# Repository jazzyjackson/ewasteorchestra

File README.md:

ewasteorchestra
===============

A group of schematics and code for building instruments out of ewaste

<h3>USB powered Hard Drive Amplifier</h3>

<h3>Harddrive Guitar using Arduino, Firmata, and Pd-Extended</h3>

<p> Works with the latest Firmata as of 4/20/2016 as distributed with Arduino 1.6.8. Sound synthesis by <a href="http://puredata.info/downloads/pd-extended">pd-extended version 0.43.4</a>, which is apparently deprecated but I'll have to catch up another time.</p>
<p> The arduino object (a.k.a. <a href="http://puredata.info/downloads/pduino">pduino</a>) by <a href="http://www.at.or.at/hans/pd/objects.html">Hans-Christoph Steiner</a> is distributed in the same folder as harddrivepackage.pd for out of the box functionality. </p>

<p> The pd sketch takes the analog inputs of the arduino (which should have SimpleAnalogFirmata flashed to memory via the Arduino IDE) and controls the volume of six oscillator objects. The MIDI value of those oscillator objects are triggered by a USB numpad. Being that the output of the DC motors in the harddrives are AC sinewaves, and the Arduino's ADC is only positive voltage at a certain sample rate, the program sums recent samples from each input while also constantly substracting from that sum over time, so the effect is that the faster you spin the hard disk, the faster you reach max volume. As soon as the harddrive stops spinning, the sum is quickly decremented to 0.  This happens in the fade subpatch of the chordfader subpatch. It's quite ugly and I wrote it before I knew about the line~ function so its not perfect. </p>

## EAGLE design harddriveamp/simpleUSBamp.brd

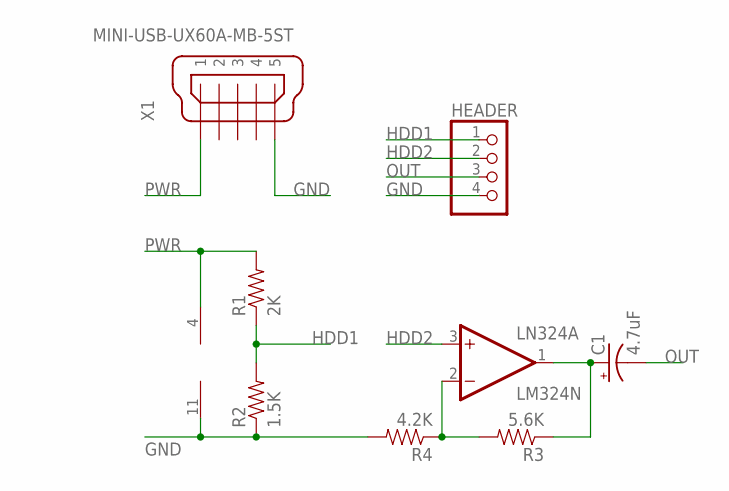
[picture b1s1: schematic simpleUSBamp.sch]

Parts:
C1: 4.7uF; CPOL-RADIAL-100UF-25V
HEADER: PINHD-1X4; 1X04
LN324: LM324N; DIL14
R1: 2K; AXIAL-0.4
R2: 1.5K; AXIAL-0.4
R3: 5.6K; AXIAL-0.4
R4: 4.2K; AXIAL-0.4
X1: MINI-USB-UX60A-MB-5ST; UX60A-MB-5ST

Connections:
GND: HEADER.4, LN324.11 (V-), R2.P$1 (1), R4.P$2 (2), X1.5
HDD1: HEADER.1, R1.P$1 (1), R2.P$2 (2)
HDD2: HEADER.2, LN324.3 (+IN)
unnamed: C1.1 (+), LN324.1 (OUT), R3.P$1 (1)
unnamed: LN324.2 (-IN), R3.P$2 (2), R4.P$1 (1)
OUT: C1.2 (-), HEADER.3
PWR: LN324.4 (V+), R1.P$2 (2), X1.1

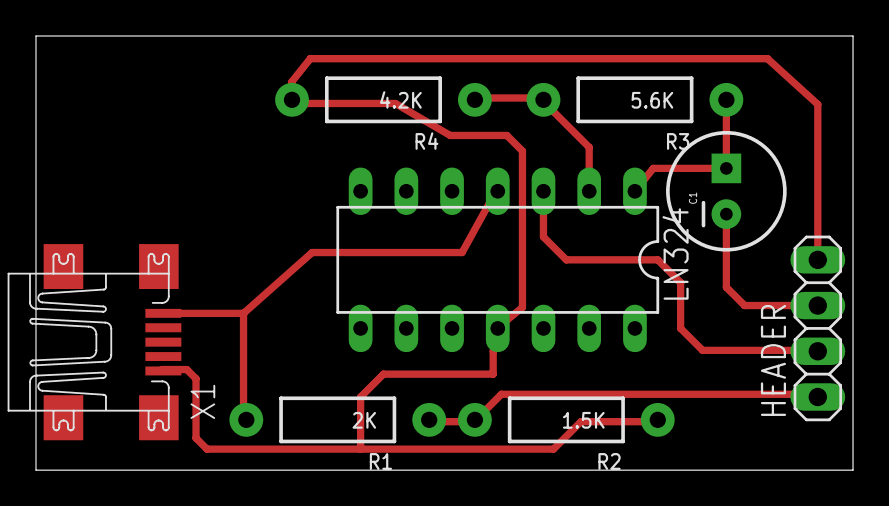
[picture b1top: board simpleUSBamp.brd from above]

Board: 2 copper layers, 45.4 x 24.1 mm, 8 parts (0 on the bottom side), 7 nets.

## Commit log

2016-04-19 Added 5V version of HDDamp
2016-04-19 Added cut files and assembly instructions
2016-04-19 Added a few photos of HDDamp USBv1
2016-04-19 Put a photo in the README
2016-04-19 Fixed bad path in readme.md
2016-04-20 Bundled the pduino object in with harddrivepackage.pd, updated README
2016-04-20 Fixed bad img path in README
2016-04-20 Added preview of pd sketch. Updated README with description of pd sketch.
2016-04-20 Fixed bad path.
2016-04-21 Created assembly instructions as pdf

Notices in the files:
parts and their libraries:
SparkFun-Capacitors: Licensing: Creative Commons ShareAlike 4.0 International - https://creativecommons.org/licenses/by-sa/4.0
